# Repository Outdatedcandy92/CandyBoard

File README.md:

## Candy Board

Candy Board is a 75% compact keyboard powered by a Raspberry Pi Pico. It includes two knobs and a oled screen on board. Along with a 75% Keyboard you have a seperated dedicated numpad.

### Inspiration

I daily drive a keychron K2 and I really love that keyboard but I really wished it had better media control keys and seperate numpad for number crunching. To address these problems I added two rotary encodes on top and a mini oled screen on the main keyboard and also designed a seperate numpad

### BOM

**Prices are in CAD unless specified**
| **Component**                                                                                                                                                                                                                                                                                                                                                                                                                                                                                                                                                                                                           | **Quantity Needed** | **Lot Price**                                             | **Unit Price** |
| ----------------------------------------------------------------------------------------------------------------------------------------------------------------------------------------------------------------------------------------------------------------------------------------------------------------------------------------------------------------------------------------------------------------------------------------------------------------------------------------------------------------------------------------------------------------------------------------------------------------------- | ------------------- | --------------------------------------------------------- | -------------- |
| [Raspberry Pi Pico Clones](https://www.aliexpress.com/item/1005003371056277.html?spm=a2g0o.productlist.main.1.1969KDf5KDf5bR&algo_pvid=55aaeefa-7c4e-48ea-a0f1-f2b9bec11f70&algo_exp_id=55aaeefa-7c4e-48ea-a0f1-f2b9bec11f70-0&pdp_ext_f=%7B%22order%22%3A%222230%22%2C%22eval%22%3A%221%22%7D&pdp_npi=4%40dis%21CAD%213.15%213.15%21%21%212.25%212.25%21%402103245417492455718148035ec6d0%2112000029224170854%21sea%21CA%216156843420%21X&curPageLogUid=erAD0Q69bg95&utparam-url=scene%3Asearch%7Cquery_from%3A)                                                                                                       | 2                   | $6.30                                                     | $3.15          |
| **PCB**                                                                                                                                                                                                                                                                                                                                                                                                                                                                                                                                                                                                                 | -                   | $44.46 + $34.91 (Shipping) - $14.03 (Coupon) = **$65.34** | -              |
| **Keyboard**                                                                                                                                                                                                                                                                                                                                                                                                                                                                                                                                                                                                            | 1                   | -                                                         | $31.84         |
| **Numpad**                                                                                                                                                                                                                                                                                                                                                                                                                                                                                                                                                                                                              | 1                   | -                                                         | $12.62         |
| **3D Case** [1 Kg Filament](https://www.amazon.ca/ELEGOO-Filament-Dimensional-Accuracy-Carboard/dp/B0CFV3WF7P?crid=2G7Q9363D6BD5&dib=eyJ2IjoiMSJ9.fFrCO7vqfw2ZbY7FFx04cCsVXbv1FeeZRx51WUK2fwS0idsI4w4F7ldKacPhSPBjlZN62jqMG53kc6guMxR63XHI2iPcLLmNgXdNF03PZQJ_CHwd6vdc23AhzuHy40twOLNul5Wm0pYRswe_AbI2aLcCYJsC3q18QWhckaqvzCFEtejY79-Tz24u0KnHFxnxsi825TP26yDtPHgsahLmyZGLz6RjSf2Mkes4hcfm0FXDZgj7BTHIp8eGl437n9-S--1w2G8q-0xxB0463m729Zk0-KcnueOy8m8zR0_S76k.ZxILjW_sPoPoCdKcvEOMj4L3A_8N23S16M6jVWlVQyk&dib_tag=se&keywords=pla%2Bmatte%2Brefill&qid=1749245436&sprefix=pla%2Bmatte%2Brefill%2Caps%2C73&sr=8-14&th=1) | 5                   | $25                                                       | -              |
| &nbsp;&nbsp;&nbsp;&nbsp;• Keyboard (Top, Bottom, Plate)                                                                                                                                                                                                                                                                                                                                                                                                                                                                                                                                                                 | 3                   | -                                                         | -              |
| &nbsp;&nbsp;&nbsp;&nbsp;• Numpad (Case, Plate)                                                                                                                                                                                                                                                                                                                                                                                                                                                                                                                                                                          | 2                   | -                                                         | -              |
| **Acrylic Cutout**                                                                                                                                                                                                                                                                                                                                                                                                                                                                                                                                                                                                      | 2                   | -                                                         | -              |
| &nbsp;&nbsp;&nbsp;&nbsp;• Keyboard                                                                                                                                                                                                                                                                                                                                                                                                                                                                                                                                                                                      | 1                   | -                                                         | -              |
| &nbsp;&nbsp;&nbsp;&nbsp;• Numpad                                                                                                                                                                                                                                                                                                                                                                                                                                                                                                                                                                                        | 1                   | -                                                         | -              |
| [EC11 15mm Rotary Encoder](https://www.aliexpress.com/item/1005005721641382.html)                                                                                                                                                                                                                                                                                                                                                                                                                                                                                                                                       | 2                   | $5.34                                                     | ~$1.00         |
| [MCP23017](https://www.aliexpress.com/item/1005005363863079.html)                                                                                                                                                                                                                                                                                                                                                                                                                                                                                                                                                       | 1                   | $4.42                                                     | $4.42          |
| [1N4148](https://www.aliexpress.com/item/1005002339916163.html)                                                                                                                                                                                                                                                                                                                                                                                                                                                                                                                                                         | 101                 | $1.27                                                     | $0.13          |
| [Cherry MX Red](https://www.aliexpress.com/item/1005006255961111.html)                                                                                                                                                                                                                                                                                                                                                                                                                                                                                                                                                  | 101                 | $39.22                                                    | $0.35          |
| [Keycaps](https://www.aliexpress.com/item/1005007393936770.html)                                                                                                                                                                                                                                                                                                                                                                                                                                                                                                                                                        | 1 set               | $31.18                                                    | $31.18         |
| [Stabilizer Set](https://www.aliexpress.com/item/1005001686319745.html)                                                                                                                                                                                                                                                                                                                                                                                                                                                                                                                                                 | 1 set               | $8.67                                                     | $8.67          |
| [SSD1306 0.91'' OLED](https://www.aliexpress.com/item/1005007302239124.html)                                                                                                                                                                                                                                                                                                                                                                                                                                                                                                                                            | 1                   | $4.42                                                     | $4.42          |
| [SK6812 Mini-E](https://www.aliexpress.com/item/1005005193716172.html)                                                                                                                                                                                                                                                                                                                                                                                                                                                                                                                                                  | 8                   | $3.18                                                     | $0.16          |
| [Rubber Feet](https://www.aliexpress.com/item/1005006211282720.html)                                                                                                                                                                                                                                                                                                                                                                                                                                                                                                                                                    | 2 sets              | $8.02                                                     | $4.01          |
| [EVA Foam](https://www.aliexpress.com/item/1005002856054113.html)                                                                                                                                                                                                                                                                                                                                                                                                                                                                                                                                                       | 1                   | $6.79                                                     | $6.79          |
| **Sub Total**                                                                                                                                                                                                                                                                                                                                                                                                                                                                                                                                                                                                           | -                   | **~$210**                                                 | -              |
| **Taxes (13%)**                                                                                                                                                                                                                                                                                                                                                                                                                                                                                                                                                                                                         | -                   | **~$27**                                                  | -              |
| **Grand Total**                                                                                                                                                                                                                                                                                                                                                                                                                                                                                                                                                                                                         | -                   | **~$237** = $174 USD                                         | -              |

### CAD Model:

### PCB & Schematic

### Firmware

Firmware was written using kmk. (no idea if it work rn tho)

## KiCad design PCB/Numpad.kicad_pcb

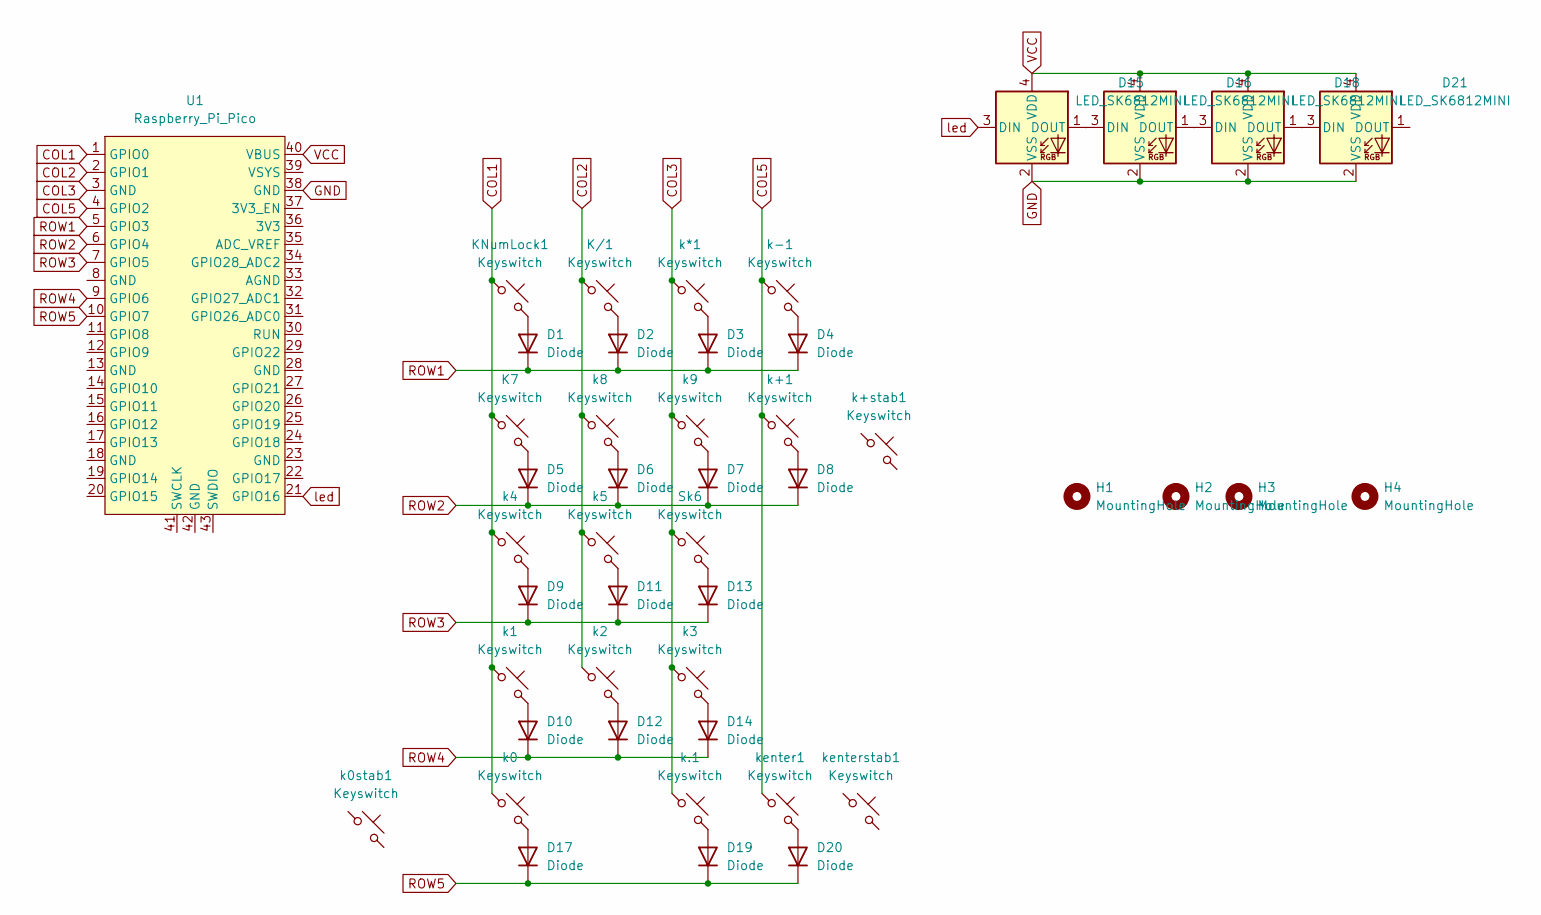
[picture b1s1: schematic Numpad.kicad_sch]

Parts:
D1, D2, D3, D4, D5, D6, D7, D8, D9, D10, D11, D12, D13, D14, D17, D19, D20: Diode; Diode_DO-35
D15, D16, D18, D21: LED_SK6812MINI
H1, H2, H3, H4: MountingHole; MountingHole_2.2mm_M2
K7: Keyswitch; MX_PCB_1.00u
K/1: Keyswitch; MX_PCB_1.00u
KNumLock1: Keyswitch; MX_PCB_1.00u
Sk6: Keyswitch; MX_PCB_1.00u
U1: Raspberry_Pi_Pico
k0: Keyswitch; MX_PCB_2.00u
k0stab1: Keyswitch; Stabilizer_MX_2.00u
k1, k2, k3, k4, k5, k8, k9, k.1: Keyswitch; MX_PCB_1.00u
k*1: Keyswitch; MX_PCB_1.00u
k+1: Keyswitch; MX_PCB_2.00u_90deg
k+stab1: Keyswitch; Stabilizer_MX_2.00u
k-1: Keyswitch; MX_PCB_1.00u
kenter1: Keyswitch; MX_PCB_2.00u_90deg
kenterstab1: Keyswitch; Stabilizer_MX_2.00u

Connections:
COL1: K7.1, KNumLock1.1, U1.1 (GPIO0), k0.1, k1.1, k4.1
COL2: K/1.1, U1.2 (GPIO1), k2.1, k5.1, k8.1
COL3: Sk6.1, U1.3 (GND), k3.1, k9.1, k*1.1, k.1.1
COL5: U1.4 (GPIO2), k+1.1, k-1.1, kenter1.1
GND: D15.2 (VSS), D16.2 (VSS), D18.2 (VSS), D21.2 (VSS), U1.38 (GND)
unnamed: D1.2 (A), KNumLock1.2
unnamed: D2.2 (A), K/1.2
unnamed: D3.2 (A), k*1.2
unnamed: D4.2 (A), k-1.2
unnamed: D5.2 (A), K7.2
unnamed: D6.2 (A), k8.2
unnamed: D7.2 (A), k9.2
unnamed: D8.2 (A), k+1.2
unnamed: D9.2 (A), k4.2
unnamed: D10.2 (A), k1.2
unnamed: D11.2 (A), k5.2
unnamed: D12.2 (A), k2.2
unnamed: D13.2 (A), Sk6.2
unnamed: D14.2 (A), k3.2
unnamed: D15.1 (DOUT), D16.3 (DIN)
unnamed: D16.1 (DOUT), D18.3 (DIN)
unnamed: D17.2 (A), k0.2
unnamed: D18.1 (DOUT), D21.3 (DIN)
unnamed: D19.2 (A), k.1.2
unnamed: D20.2 (A), kenter1.2
ROW1: D1.1 (K), D2.1 (K), D3.1 (K), D4.1 (K), U1.5 (GPIO3)
ROW2: D5.1 (K), D6.1 (K), D7.1 (K), D8.1 (K), U1.6 (GPIO4)
ROW3: D9.1 (K), D11.1 (K), D13.1 (K), U1.7 (GPIO5)
ROW4: D10.1 (K), D12.1 (K), D14.1 (K), U1.9 (GPIO6)
ROW5: D17.1 (K), D19.1 (K), D20.1 (K), U1.10 (GPIO7)
VCC: D15.4 (VDD), D16.4 (VDD), D18.4 (VDD), D21.4 (VDD), U1.40 (VBUS)
led: D15.3 (DIN), U1.21 (GPIO16)

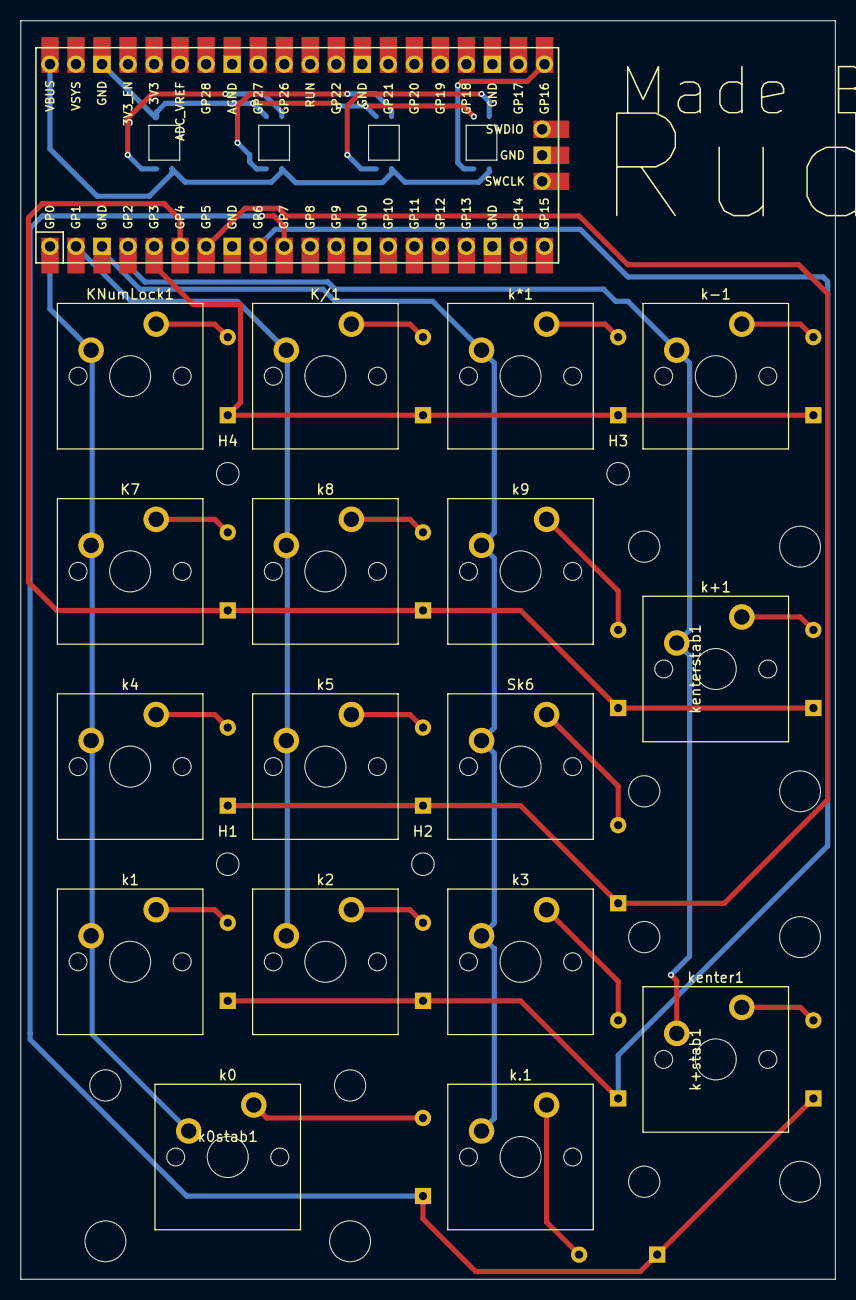
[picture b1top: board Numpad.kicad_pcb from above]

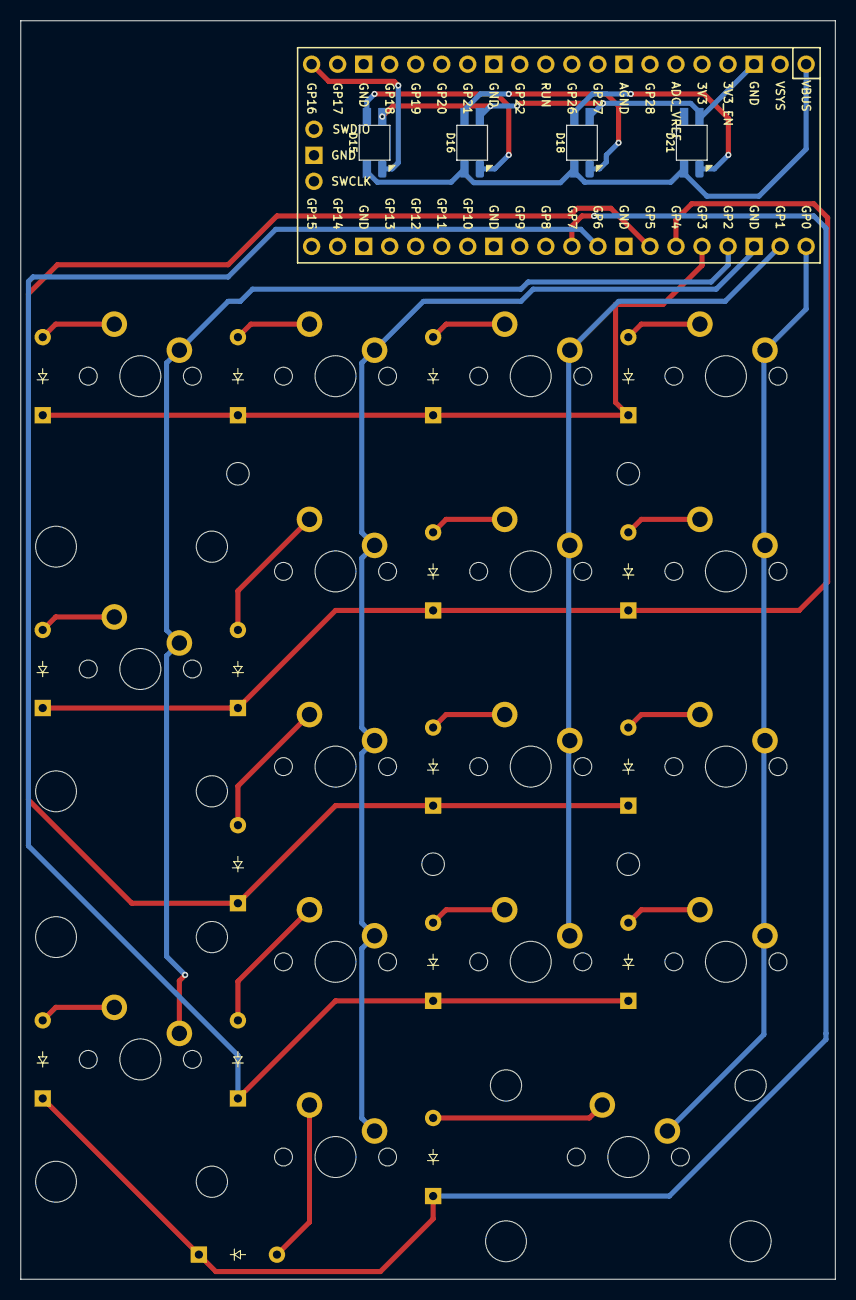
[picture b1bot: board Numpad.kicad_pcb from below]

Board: 2 copper layers, 79.5 x 122.8 mm, 46 parts (17 on the bottom side), 32 nets.

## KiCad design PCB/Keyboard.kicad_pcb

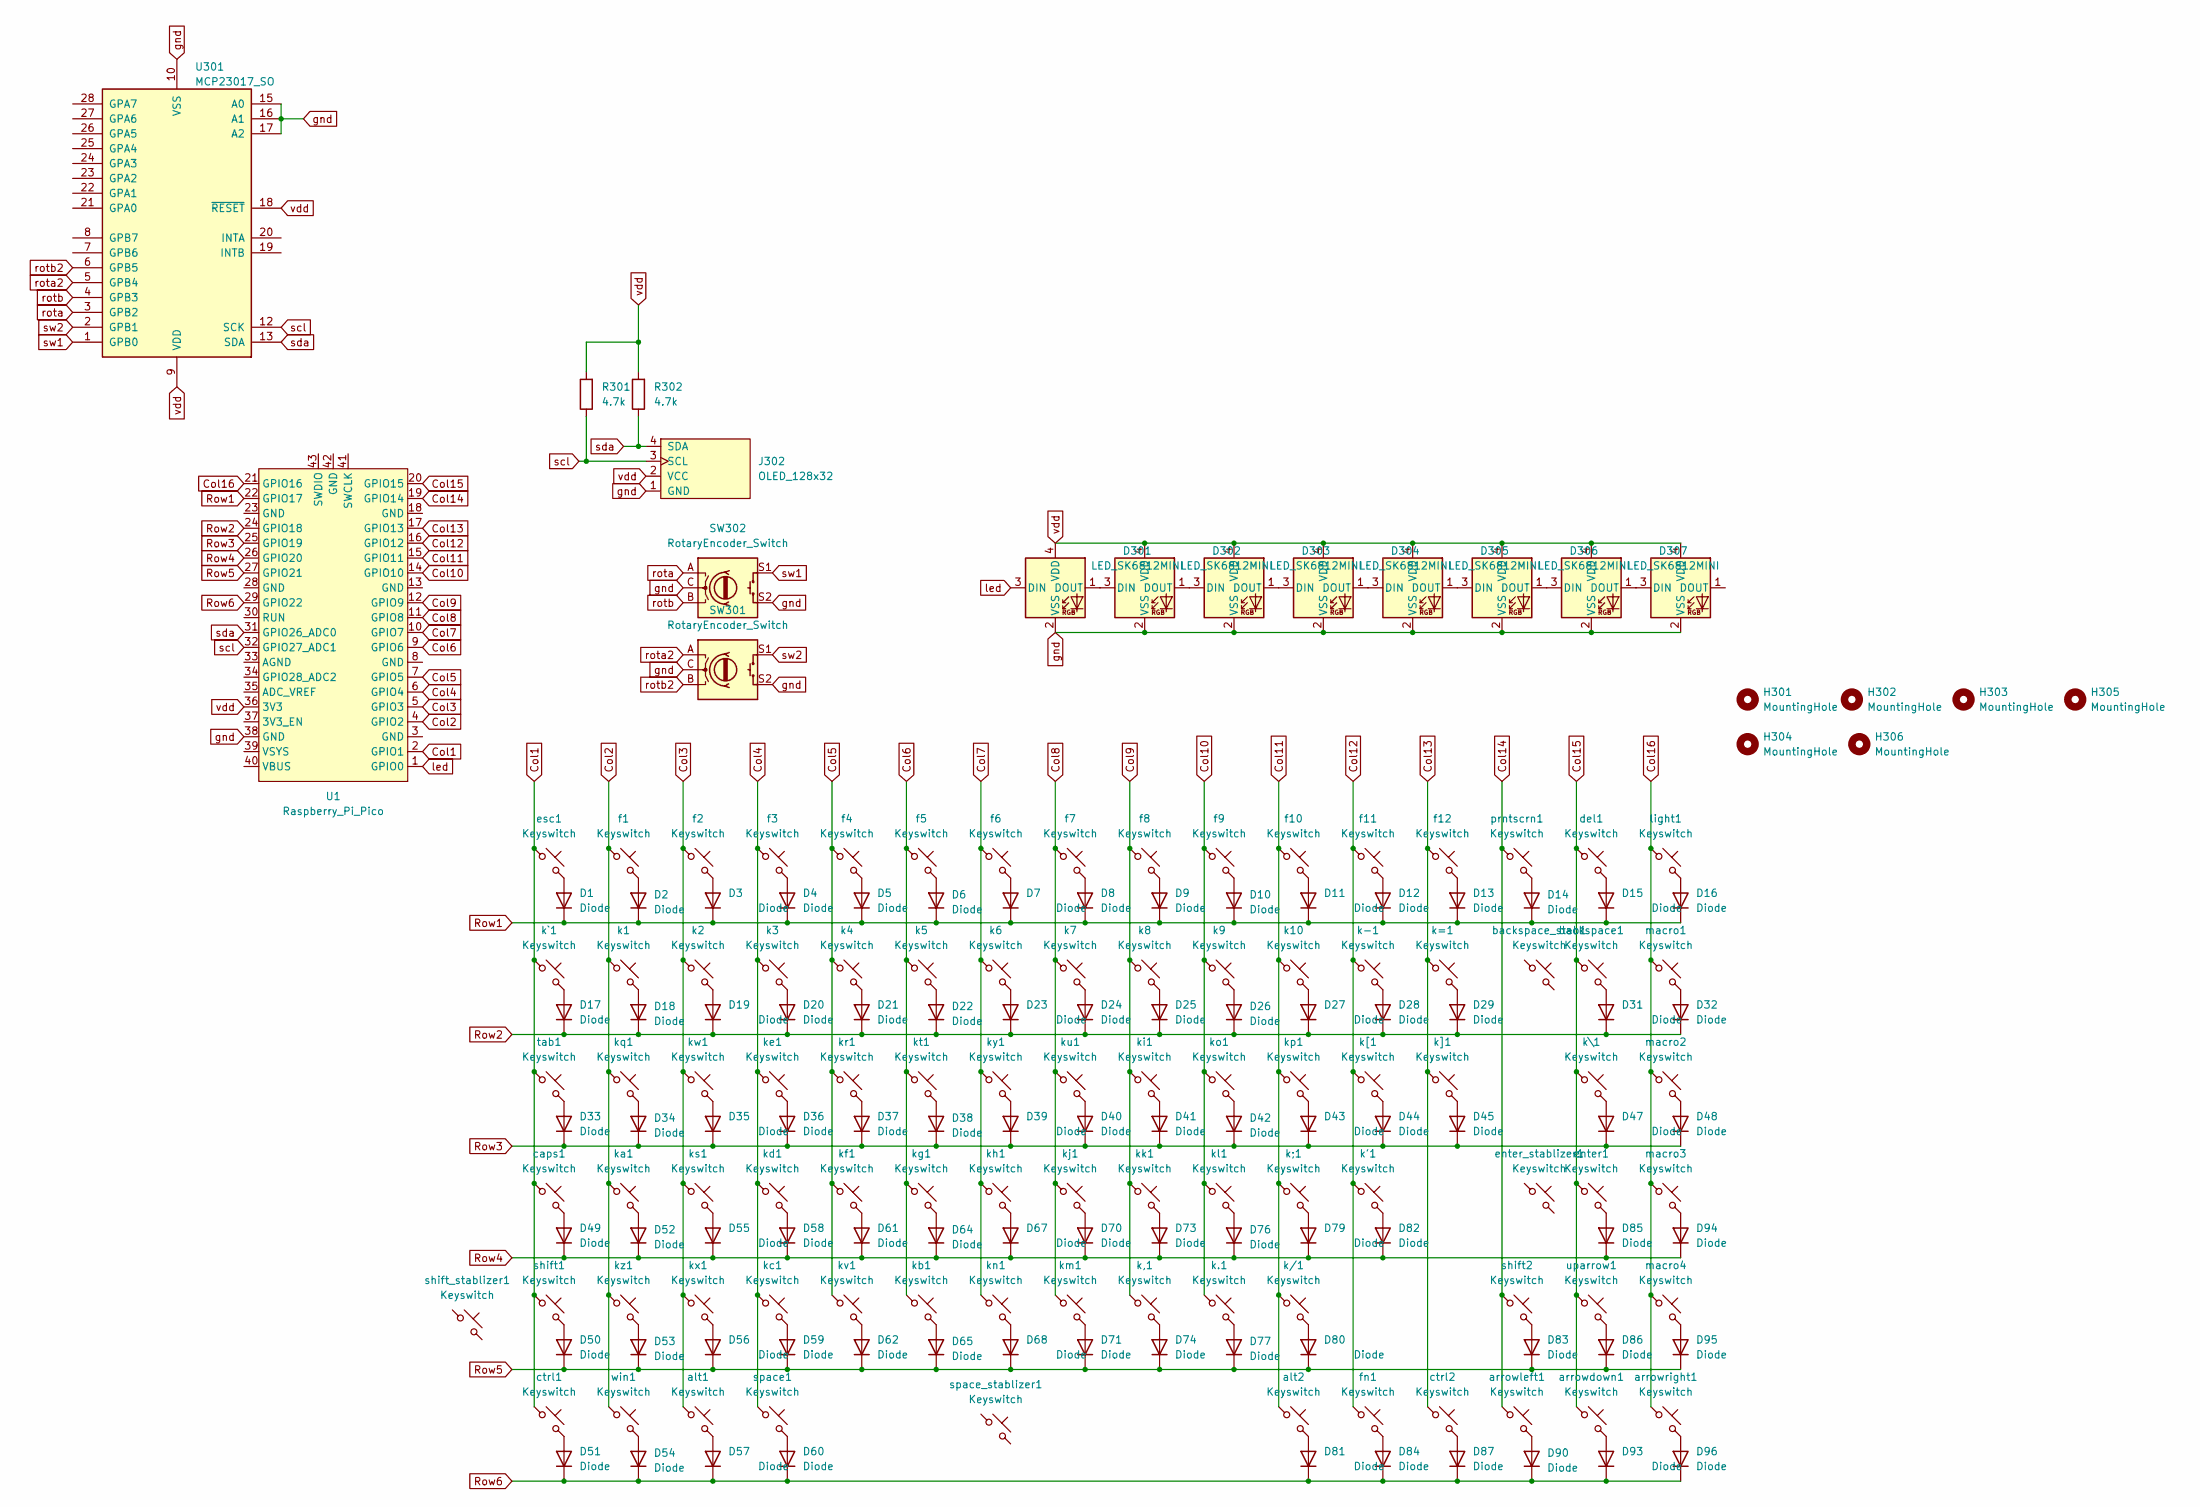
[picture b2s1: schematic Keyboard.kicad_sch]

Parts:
D1, D2, D3, D4, D5, D6, D7, D8, D9, D10, D11, D12, D13, D14, D15, D16, D17, D18, D19, D20, D21, D22, D23, D24, D25, D26, D27, D28, D29, D31, D32, D33, D34, D35, D36, D37, D38, D39, D40, D41, D42, D43, D44, D45, D47, D48, D49, D50, D51, D52, D53, D54, D55, D56, D57, D58, D59, D60, D61, D62, D64, D65, D67, D68, D70, D71, D73, D74, D76, D77, D79, D80, D81, D82, D83, D84, D85, D86, D87, D90, D93, D94, D95, D96: Diode; Diode_DO-35
D301, D302, D303, D304, D305, D306, D307, D308: LED_SK6812MINI
H301, H302, H303, H304, H305, H306: MountingHole; MountingHole_2.2mm_M2
J302: OLED_128x32
R301, R302: 4.7k; R_Axial_DIN0204_L3.6mm_D1.6mm_P1.90mm_Vertical
SW301, SW302: RotaryEncoder_Switch; RotaryEncoder_Alps_EC12E-Switch_Vertical_H20mm
U1: Raspberry_Pi_Pico
U301: MCP23017_SO; SOIC-28W_7.5x17.9mm_P1.27mm
alt1: Keyswitch; MX_PCB_1.25u
alt2: Keyswitch; MX_PCB_1.00u
arrowdown1: Keyswitch; MX_PCB_1.00u
arrowleft1: Keyswitch; MX_PCB_1.00u
arrowright1: Keyswitch; MX_PCB_1.00u
backspace1: Keyswitch; MX_PCB_2.00u
backspace_stab1: Keyswitch; Stabilizer_MX_2.00u
caps1: Keyswitch; MX_PCB_1.75u
ctrl1: Keyswitch; MX_PCB_1.25u
ctrl2: Keyswitch; MX_PCB_1.00u
del1: Keyswitch; MX_PCB_1.00u
enter1: Keyswitch; MX_PCB_2.25u
enter_stablizer1: Keyswitch; Stabilizer_MX_2.00u
esc1: Keyswitch; MX_PCB_1.00u
f1, f2, f3, f4, f5, f6, f7, f8, f9, f10, f11, f12: Keyswitch; MX_PCB_1.00u
fn1: Keyswitch; MX_PCB_1.00u
k1, k2, k3, k4, k5, k6, k7, k8, k9, k10, k.1: Keyswitch; MX_PCB_1.00u
k'1: Keyswitch; MX_PCB_1.00u
k,1: Keyswitch; MX_PCB_1.00u
k-1: Keyswitch; MX_PCB_1.00u
k/1: Keyswitch; MX_PCB_1.00u
k;1: Keyswitch; MX_PCB_1.00u
k=1: Keyswitch; MX_PCB_1.00u
k[1: Keyswitch; MX_PCB_1.00u
k\1: Keyswitch; MX_PCB_1.50u
k]1: Keyswitch; MX_PCB_1.00u
k`1: Keyswitch; MX_PCB_1.00u
ka1: Keyswitch; MX_PCB_1.00u
kb1: Keyswitch; MX_PCB_1.00u
kc1: Keyswitch; MX_PCB_1.00u
kd1: Keyswitch; MX_PCB_1.00u
ke1: Keyswitch; MX_PCB_1.00u
kf1: Keyswitch; MX_PCB_1.00u
kg1: Keyswitch; MX_PCB_1.00u
kh1: Keyswitch; MX_PCB_1.00u
ki1: Keyswitch; MX_PCB_1.00u
kj1: Keyswitch; MX_PCB_1.00u
kk1: Keyswitch; MX_PCB_1.00u
kl1: Keyswitch; MX_PCB_1.00u
km1: Keyswitch; MX_PCB_1.00u
kn1: Keyswitch; MX_PCB_1.00u
ko1: Keyswitch; MX_PCB_1.00u
kp1: Keyswitch; MX_PCB_1.00u
kq1: Keyswitch; MX_PCB_1.00u
kr1: Keyswitch; MX_PCB_1.00u
ks1: Keyswitch; MX_PCB_1.00u
kt1: Keyswitch; MX_PCB_1.00u
ku1: Keyswitch; MX_PCB_1.00u
kv1: Keyswitch; MX_PCB_1.00u
kw1: Keyswitch; MX_PCB_1.00u
kx1: Keyswitch; MX_PCB_1.00u
ky1: Keyswitch; MX_PCB_1.00u
kz1: Keyswitch; MX_PCB_1.00u
light1: Keyswitch; MX_PCB_1.00u
macro1, macro2, macro3, macro4: Keyswitch; MX_PCB_1.00u
prntscrn1: Keyswitch; MX_PCB_1.00u
shift1: Keyswitch; MX_PCB_2.25u
shift2: Keyswitch; MX_PCB_1.75u
shift_stablizer1: Keyswitch; Stabilizer_MX_2.00u
space1: Keyswitch; MX_PCB_6.25u
space_stablizer1: Keyswitch; Stabilizer_MX_6.25u
tab1: Keyswitch; MX_PCB_1.50u
uparrow1: Keyswitch; MX_PCB_1.00u
win1: Keyswitch; MX_PCB_1.25u

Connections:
Col1: U1.2 (GPIO1), caps1.1, ctrl1.1, esc1.1, k`1.1, shift1.1, tab1.1
Col2: U1.4 (GPIO2), f1.1, k1.1, ka1.1, kq1.1, kz1.1, win1.1
Col3: U1.5 (GPIO3), alt1.1, f2.1, k2.1, ks1.1, kw1.1, kx1.1
Col4: U1.6 (GPIO4), f3.1, k3.1, kc1.1, kd1.1, ke1.1, space1.1
Col5: U1.7 (GPIO5), f4.1, k4.1, kf1.1, kr1.1, kv1.1
Col6: U1.9 (GPIO6), f5.1, k5.1, kb1.1, kg1.1, kt1.1
Col7: U1.10 (GPIO7), f6.1, k6.1, kh1.1, kn1.1, ky1.1
Col8: U1.11 (GPIO8), f7.1, k7.1, kj1.1, km1.1, ku1.1
Col9: U1.12 (GPIO9), f8.1, k8.1, k,1.1, ki1.1, kk1.1
Col10: U1.14 (GPIO10), f9.1, k9.1, k.1.1, kl1.1, ko1.1
Col11: U1.15 (GPIO11), alt2.1, f10.1, k10.1, k/1.1, k;1.1, kp1.1
Col12: U1.16 (GPIO12), f11.1, fn1.1, k'1.1, k-1.1, k[1.1
Col13: U1.17 (GPIO13), ctrl2.1, f12.1, k=1.1, k]1.1
Col14: U1.19 (GPIO14), arrowleft1.1, prntscrn1.1, shift2.1
Col15: U1.20 (GPIO15), arrowdown1.1, backspace1.1, del1.1, enter1.1, k\1.1, uparrow1.1
Col16: U1.21 (GPIO16), arrowright1.1, light1.1, macro1.1, macro2.1, macro3.1, macro4.1
unnamed: D1.2 (A), esc1.2
unnamed: D2.2 (A), f1.2
unnamed: D3.2 (A), f2.2
unnamed: D4.2 (A), f3.2
unnamed: D5.2 (A), f4.2
unnamed: D6.2 (A), f5.2
unnamed: D7.2 (A), f6.2
unnamed: D8.2 (A), f7.2
unnamed: D9.2 (A), f8.2
unnamed: D10.2 (A), f9.2
unnamed: D11.2 (A), f10.2
unnamed: D12.2 (A), f11.2
unnamed: D13.2 (A), f12.2
unnamed: D14.2 (A), prntscrn1.2
unnamed: D15.2 (A), del1.2
unnamed: D16.2 (A), light1.2
unnamed: D17.2 (A), k`1.2
unnamed: D18.2 (A), k1.2
unnamed: D19.2 (A), k2.2
unnamed: D20.2 (A), k3.2
unnamed: D21.2 (A), k4.2
unnamed: D22.2 (A), k5.2
unnamed: D23.2 (A), k6.2
unnamed: D24.2 (A), k7.2
unnamed: D25.2 (A), k8.2
unnamed: D26.2 (A), k9.2
unnamed: D27.2 (A), k10.2
unnamed: D28.2 (A), k-1.2
unnamed: D29.2 (A), k=1.2
unnamed: D31.2 (A), backspace1.2
unnamed: D32.2 (A), macro1.2
unnamed: D33.2 (A), tab1.2
unnamed: D34.2 (A), kq1.2
unnamed: D35.2 (A), kw1.2
unnamed: D36.2 (A), ke1.2
unnamed: D37.2 (A), kr1.2
unnamed: D38.2 (A), kt1.2
unnamed: D39.2 (A), ky1.2
unnamed: D40.2 (A), ku1.2
unnamed: D41.2 (A), ki1.2
unnamed: D42.2 (A), ko1.2
unnamed: D43.2 (A), kp1.2
unnamed: D44.2 (A), k[1.2
unnamed: D45.2 (A), k]1.2
unnamed: D47.2 (A), k\1.2
unnamed: D48.2 (A), macro2.2
unnamed: D49.2 (A), caps1.2
unnamed: D50.2 (A), shift1.2
unnamed: D51.2 (A), ctrl1.2
unnamed: D52.2 (A), ka1.2
unnamed: D53.2 (A), kz1.2
unnamed: D54.2 (A), win1.2
unnamed: D55.2 (A), ks1.2
unnamed: D56.2 (A), kx1.2
unnamed: D57.2 (A), alt1.2
unnamed: D58.2 (A), kd1.2
unnamed: D59.2 (A), kc1.2
unnamed: D60.2 (A), space1.2
unnamed: D61.2 (A), kf1.2
unnamed: D62.2 (A), kv1.2
unnamed: D64.2 (A), kg1.2
unnamed: D65.2 (A), kb1.2
unnamed: D67.2 (A), kh1.2
unnamed: D68.2 (A), kn1.2
unnamed: D70.2 (A), kj1.2
unnamed: D71.2 (A), km1.2
unnamed: D73.2 (A), kk1.2
unnamed: D74.2 (A), k,1.2
unnamed: D76.2 (A), kl1.2
unnamed: D77.2 (A), k.1.2
unnamed: D79.2 (A), k;1.2
unnamed: D80.2 (A), k/1.2
unnamed: D81.2 (A), alt2.2
unnamed: D82.2 (A), k'1.2
unnamed: D83.2 (A), shift2.2
unnamed: D84.2 (A), fn1.2
unnamed: D85.2 (A), enter1.2
unnamed: D86.2 (A), uparrow1.2
unnamed: D87.2 (A), ctrl2.2
unnamed: D90.2 (A), arrowleft1.2
unnamed: D93.2 (A), arrowdown1.2
unnamed: D94.2 (A), macro3.2
unnamed: D95.2 (A), macro4.2
unnamed: D96.2 (A), arrowright1.2
unnamed: D301.1 (DOUT), D302.3 (DIN)
unnamed: D302.1 (DOUT), D303.3 (DIN)
unnamed: D303.1 (DOUT), D304.3 (DIN)
unnamed: D304.1 (DOUT), D305.3 (DIN)
unnamed: D305.1 (DOUT), D306.3 (DIN)
unnamed: D306.1 (DOUT), D307.3 (DIN)
unnamed: D307.1 (DOUT), D308.3 (DIN)
Row1: D1.1 (K), D2.1 (K), D3.1 (K), D4.1 (K), D5.1 (K), D6.1 (K), D7.1 (K), D8.1 (K), D9.1 (K), D10.1 (K), D11.1 (K), D12.1 (K), D13.1 (K), D14.1 (K), D15.1 (K), D16.1 (K), U1.22 (GPIO17)
Row2: D17.1 (K), D18.1 (K), D19.1 (K), D20.1 (K), D21.1 (K), D22.1 (K), D23.1 (K), D24.1 (K), D25.1 (K), D26.1 (K), D27.1 (K), D28.1 (K), D29.1 (K), D31.1 (K), D32.1 (K), U1.24 (GPIO18)
Row3: D33.1 (K), D34.1 (K), D35.1 (K), D36.1 (K), D37.1 (K), D38.1 (K), D39.1 (K), D40.1 (K), D41.1 (K), D42.1 (K), D43.1 (K), D44.1 (K), D45.1 (K), D47.1 (K), D48.1 (K), U1.25 (GPIO19)
Row4: D49.1 (K), D52.1 (K), D55.1 (K), D58.1 (K), D61.1 (K), D64.1 (K), D67.1 (K), D70.1 (K), D73.1 (K), D76.1 (K), D79.1 (K), D82.1 (K), D85.1 (K), D94.1 (K), U1.26 (GPIO20)
Row5: D50.1 (K), D53.1 (K), D56.1 (K), D59.1 (K), D62.1 (K), D65.1 (K), D68.1 (K), D71.1 (K), D74.1 (K), D77.1 (K), D80.1 (K), D83.1 (K), D86.1 (K), D95.1 (K), U1.27 (GPIO21)
Row6: D51.1 (K), D54.1 (K), D57.1 (K), D60.1 (K), D81.1 (K), D84.1 (K), D87.1 (K), D90.1 (K), D93.1 (K), D96.1 (K), U1.29 (GPIO22)
gnd: D301.2 (VSS), D302.2 (VSS), D303.2 (VSS), D304.2 (VSS), D305.2 (VSS), D306.2 (VSS), D307.2 (VSS), D308.2 (VSS), J302.1 (GND), SW301.C, SW301.S2, SW302.C, SW302.S2, U1.38 (GND), U301.10 (VSS), U301.15 (A0), U301.16 (A1), U301.17 (A2)
led: D301.3 (DIN), U1.1 (GPIO0)
rota: SW302.A, U301.3 (GPB2)
rota2: SW301.A, U301.5 (GPB4)
rotb: SW302.B, U301.4 (GPB3)
rotb2: SW301.B, U301.6 (GPB5)
scl: J302.3 (SCL), R301.1, U1.32 (GPIO27_ADC1), U301.12 (SCK)
sda: J302.4 (SDA), R302.1, U1.31 (GPIO26_ADC0), U301.13 (SDA)
sw1: SW302.S1, U301.1 (GPB0)
sw2: SW301.S1, U301.2 (GPB1)
vdd: D301.4 (VDD), D302.4 (VDD), D303.4 (VDD), D304.4 (VDD), D305.4 (VDD), D306.4 (VDD), D307.4 (VDD), D308.4 (VDD), J302.2 (VCC), R301.2, R302.2, U1.36 (3V3), U301.9 (VDD), U301.18 (~RESET)

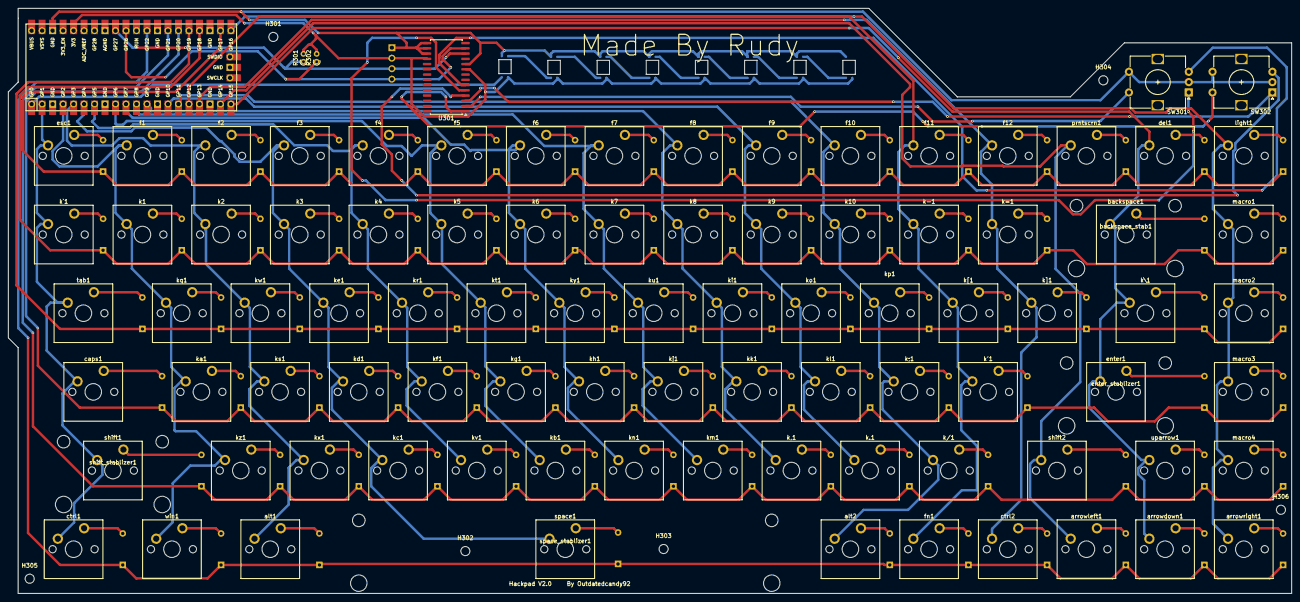
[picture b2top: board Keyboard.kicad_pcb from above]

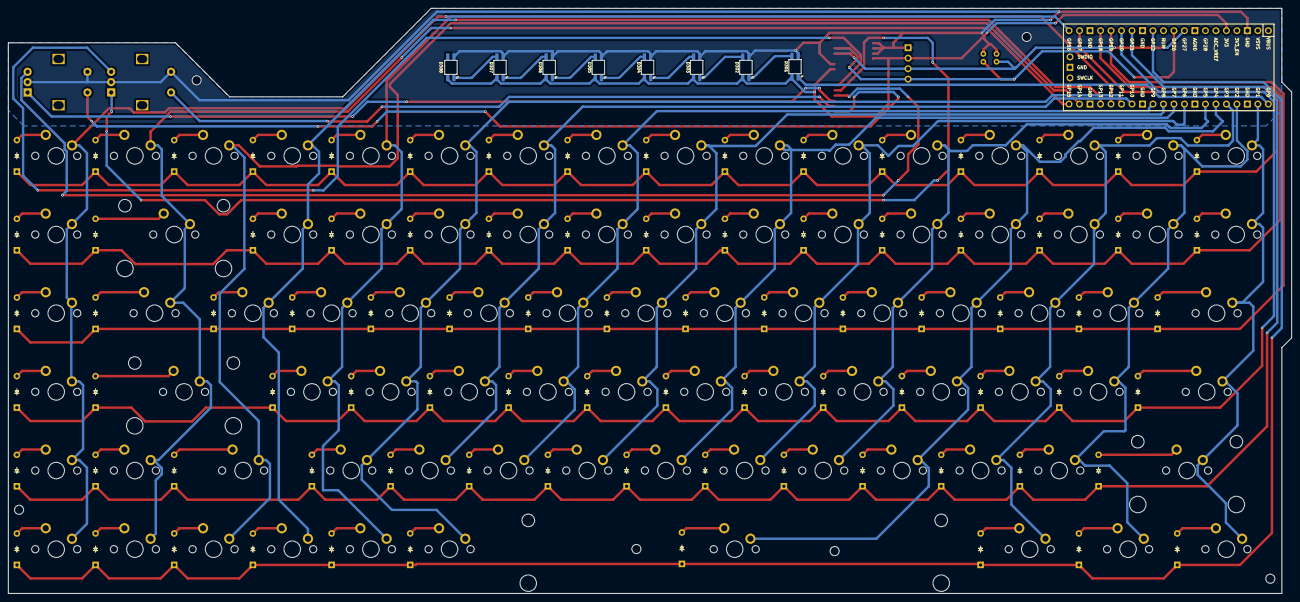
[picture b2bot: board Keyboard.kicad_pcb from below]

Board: 2 copper layers, 310.8 x 141.7 mm, 193 parts (84 on the bottom side), 124 nets.
